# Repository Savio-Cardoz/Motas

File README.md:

# Motas
Code for Motas controller with Ultrasonic, PIR and sd card implemented

Functions the abstraction layer can use.

To get the Time Count of Ultrasonic Sensor
  uint16_t Get_Uss_Count();    returns an integer with time count equivalent to distance
  
  uint16_t Get_Pir_Count();    returns an integer with the current count of PIR sensor triggers
  
  void Reset_Pir_Count();
  
  void Dfplayer_Cmd(uint8_t cmd, uint16_t parameter);   Takes command with parameter value for that command
  
  ***** Pending addition of 'reading status of DF player to enter debug mode *******

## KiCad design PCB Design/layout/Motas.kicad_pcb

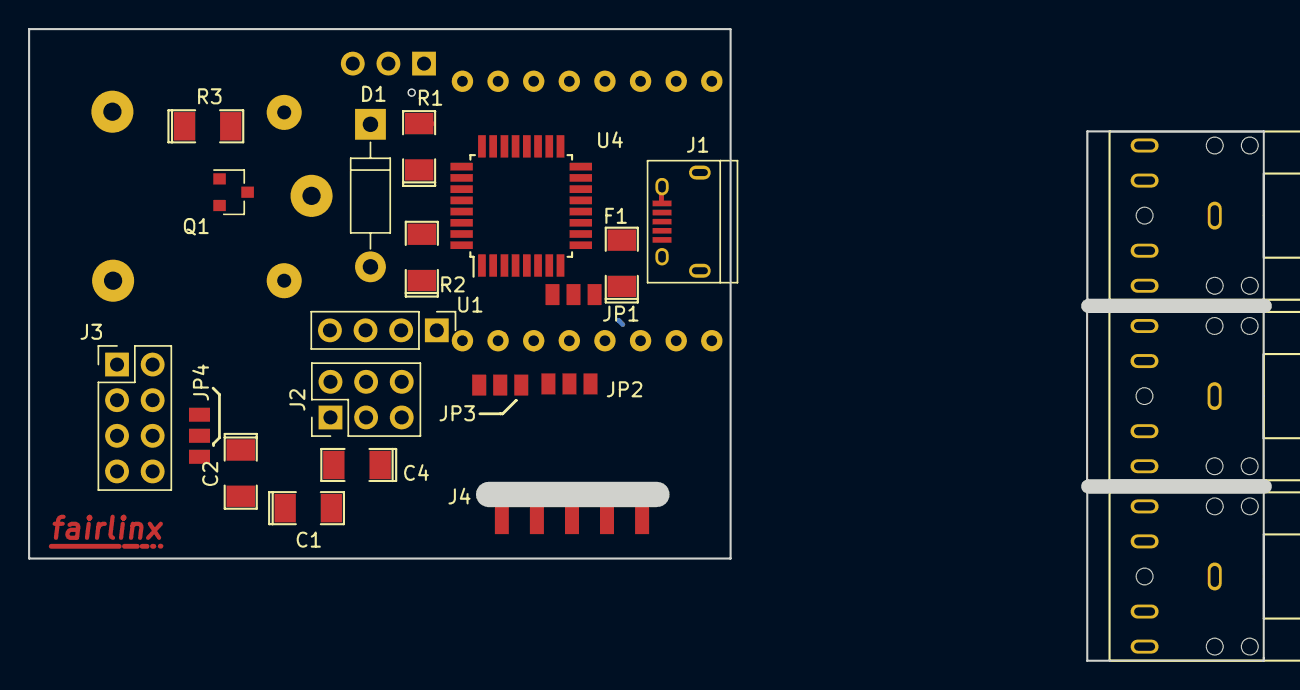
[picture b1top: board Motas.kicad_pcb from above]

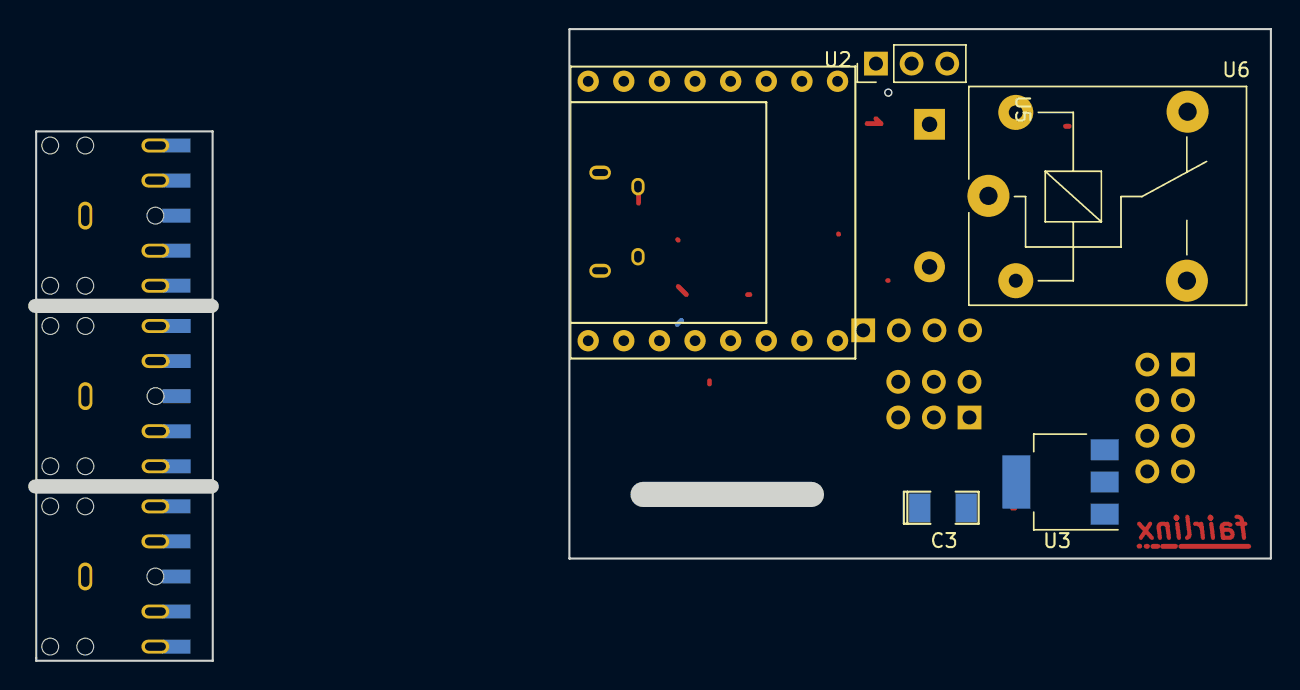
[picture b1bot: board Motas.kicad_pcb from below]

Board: 2 copper layers, 86.9 x 43.4 mm, 24 parts (5 on the bottom side), 36 nets.

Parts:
C1, C2, C3, C4: SMD-1206_Pol
D1: D_DO-41_SOD81_P10.16mm_Horizontal
F1: SMD-1206_Pol
J1: USB_Micro-B
J2: Pin_Header_Straight_2x03_Pitch2.54mm
J3: Pin_Header_Straight_2x04_Pitch2.54mm
J4: special_con_audio_socket_PCB
JP1, JP2, JP3, JP4: Jumper_3Pin_SMD
Q1: SOT-23
R1, R2, R3: SMD-1206_Pol
U1: Pin_Header_Straight_1x04_Pitch2.54mm
U2: Pin_Header_Straight_1x03_Pitch2.54mm
U3: SOT-223-3Lead_TabPin2
U4: TQFP-32_7x7mm_Pitch0.8mm
U5: DFPlayer
U6: Relay_SPDT_SANYOU_SRD_Series_Form_C

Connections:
+5V: C3.1, C4.1, D1.1, JP1.2, R1.2, U1.1, U2.1, U4.4, U4.6, U5.1, U6.5
BUSY_CONTRL: U4.19, U5.16
ECHO_CONTRL: U1.3, U4.32
GND: C1.2, C2.2, C3.2, C4.2, J1.5, J1.6, J2.6, J3.7, J4.1, Q1.2, U1.4, U2.3, U3.1, U4.3, U4.5, U5.7, U5.10
GPIO1: J3.3, U4.23
GPIO2: J3.4, U4.24
GPIO3/DBG_TX: J3.1, U4.27
GPIO4/DBG_RX: J3.2, U4.28
IO1_CONTRL: U4.25, U5.9
IO2_CONTRL: U4.26, U5.11
MISO: J2.5, U4.16
MOSI: J2.3, U4.15
unnamed: C1.1, JP1.3, U3.2
unnamed: D1.2, Q1.3, U6.2
unnamed: F1.1, JP1.1
unnamed: F1.2, J1.1
unnamed: J4.2, JP3.2
unnamed: J4.3, JP2.2
unnamed: JP2.1, U5.4
unnamed: JP2.3, U5.6
unnamed: JP3.1, U5.5
unnamed: JP3.3, U5.8
unnamed: JP4.1, U6.4
unnamed: JP4.3, U6.3
unnamed: Q1.1, R3.1
unnamed: R2.1, U5.2
PIR_CONTRL: U2.2, U4.1
POWER_IN: C2.1, J3.8, U3.3
RL_CONTRL: R3.2, U4.12
RL_OUT_1: J3.5, U6.1
RL_OUT_2: J3.6, JP4.2
RST: J2.1, R1.1, U4.29
RX_CONTRL: U4.30, U5.3
SCK: J2.2, U4.17
TRIG_CONTRL: U1.2, U4.13
TX_CONTRL: R2.2, U4.31

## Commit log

2017-05-19 Added schematic and schematic library files
2017-05-19 Added files for the DFplayer
2017-05-20 Replaced with another file
2017-05-29 state machine implementation is partially done. Work in progress
2017-05-31 sd card and led not implemented. Doxugen format implemented for changed files.Check for compilation issues.
2017-06-04 Updated funtions
    Added function -> Get_Pir_Status, which will return the Status of motion as 1 or 0.
    Added function -> Led_On(led_color) and Led_Off(led_color).
    Modified SendDebug()
    Tested funtioning of the PIR motion, USS distance count, mp3 player command and LED control.
2017-06-22 Adding the latest 3D files
2017-06-29 Updated 3D model design
2017-07-08 Enclosure model revision. Ports at the back
2017-09-06 Files reorganised
2017-09-19 Implementation of the Debug state and added the xmind design file
2017-09-23 added software uart
2017-09-23 Added bit-field struct to use for flags
2017-09-23 Finished the implementation of the Debugging state
2017-09-23 Made changes in the state machine
2017-09-23 Can debug using LED indications
2017-09-23 merging changes
2017-09-23 Initial build
2017-09-26 updated a firmware test file
2017-09-30 resolved problem of no USS and PIR counts. Interrupts were were wrongly assigned
2017-10-01 audio play stops now on USS being triggered, USS is auto triggered after 100ms from receiving the last echo
2017-10-04 Debugging Active state failure
2017-10-15 Removed all warnings
